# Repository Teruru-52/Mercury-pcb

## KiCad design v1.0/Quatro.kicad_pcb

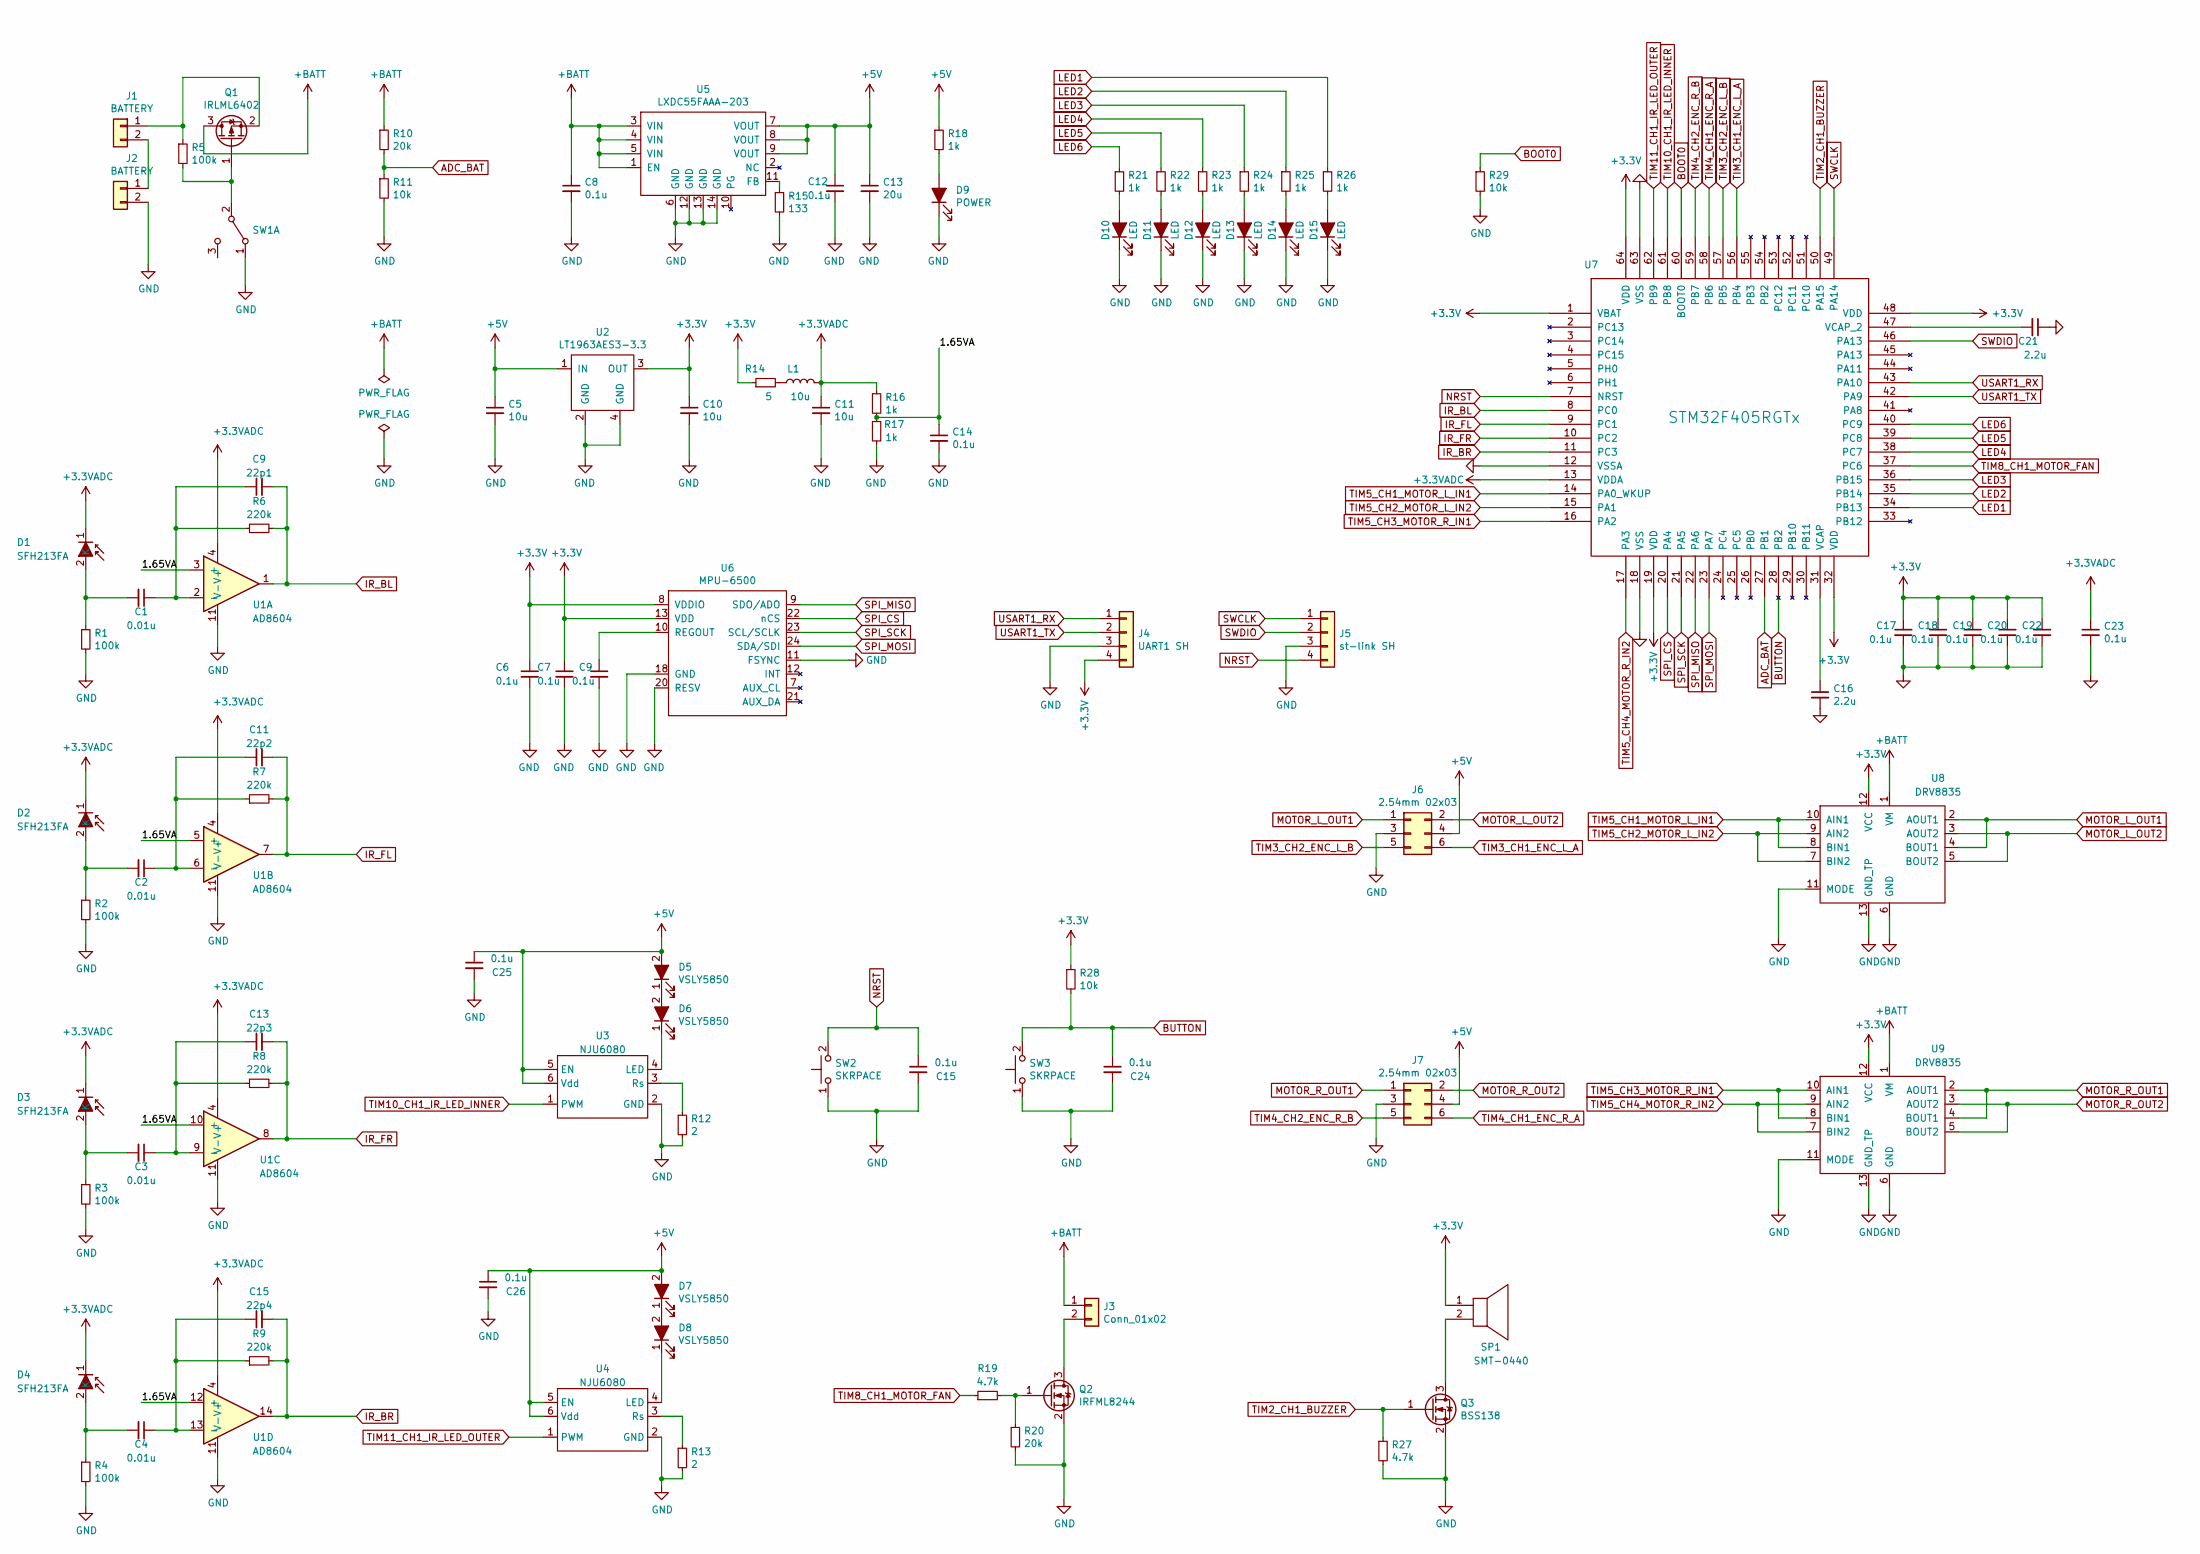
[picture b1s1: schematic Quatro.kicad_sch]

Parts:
22p1: C9; C_0603_1608Metric_Pad1.08x0.95mm_HandSolder
22p2: C11; C_0603_1608Metric_Pad1.08x0.95mm_HandSolder
22p3: C13; C_0603_1608Metric_Pad1.08x0.95mm_HandSolder
22p4: C15; C_0603_1608Metric_Pad1.08x0.95mm_HandSolder
C1, C2, C3, C4: 0.01u; C_0603_1608Metric_Pad1.08x0.95mm_HandSolder
C5, C10, C11: 10u; C_0603_1608Metric_Pad1.08x0.95mm_HandSolder
C6, C7, C8, C9, C12, C14, C15, C17, C18, C19, C20, C22, C23, C24, C25, C26: 0.1u; C_0603_1608Metric_Pad1.08x0.95mm_HandSolder
C13: 20u; C_0603_1608Metric_Pad1.08x0.95mm_HandSolder
C16, C21: 2.2u; C_0603_1608Metric_Pad1.08x0.95mm_HandSolder
D1, D2, D3, D4: SFH213FA; D_T-1_P2.54mm_Vertical_AnodeUp
D5, D6, D7, D8: VSLY5850; D_T-1_P2.54mm_Vertical_AnodeUp
D9: POWER; LED_0603_1608Metric_Pad1.05x0.95mm_HandSolder
D10, D11, D12, D13, D14, D15: LED; LED_0603_1608Metric_Pad1.05x0.95mm_HandSolder
J1, J2: BATTERY; PinSocket_1x02_P1.27mm_Vertical
J3: Conn_01x02; PinSocket_1x02_P1.27mm_Vertical
J4: UART1 SH; PinHeader_1x04_P2.54mm_Vertical
J5: st-link SH; JST_SH_BM04B-SRSS-TB_1x04-1MP_P1.00mm_Vertical
J6, J7: 2.54mm 02x03; PinHeader_2x03_P2.54mm_Vertical
L1: 10u; L_1210_3225Metric_Pad1.42x2.65mm_HandSolder
Q1: IRLML6402; SOT-23
Q2: IRFML8244; SOT-23
Q3: BSS138; SOT-23
R1, R2, R3, R4, R5: 100k; R_0805_2012Metric_Pad1.20x1.40mm_HandSolder
R6, R7, R8, R9: 220k; R_0603_1608Metric_Pad0.98x0.95mm_HandSolder
R10, R20: 20k; R_0603_1608Metric_Pad0.98x0.95mm_HandSolder
R11, R29: 10k; R_0805_2012Metric_Pad1.20x1.40mm_HandSolder
R12, R13: 2; R_0805_2012Metric_Pad1.20x1.40mm_HandSolder
R14: 5; R_0805_2012Metric_Pad1.20x1.40mm_HandSolder
R15: 133; R_1206_3216Metric_Pad1.30x1.75mm_HandSolder
R16, R17, R18, R21, R22, R23, R24, R25, R26: 1k; R_0805_2012Metric_Pad1.20x1.40mm_HandSolder
R19, R27: 4.7k; R_0603_1608Metric_Pad0.98x0.95mm_HandSolder
R28: 10k; R_0603_1608Metric_Pad0.98x0.95mm_HandSolder
SP1: SMT-0440; SMT-0440-T-R
SW1: SW_DPDT_x2; SlideSwitch
SW2, SW3: SKRPACE; SW_Push_1P1T_NO_Vertical_Wuerth_434133025816
U1: AD8604; TSSOP-14_4.4x5mm_P0.65mm
U2: LT1963AES3-3.3; SOT-223
U3, U4: NJU6080; SOT-23-6_Handsoldering
U5: LXDC55FAAA-203
U6: MPU-6500; QFN-24-1EP_3x3mm_P0.4mm_EP1.75x1.6mm
U7: STM32F405RGTx; LQFP-64_10x10mm_P0.5mm
U8, U9: DRV8835

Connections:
+3.3V: C6.1, C7.1, C10.1, C17.1, C18.1, C19.1, C20.1, C22.1, J4.4, R14.1, R28.1, SP1.1, U2.3 (OUT), U6.8 (VDDIO), U6.13 (VDD), U7.1 (VBAT), U7.19 (VDD), U7.32 (VDD), U7.48 (VDD), U7.64 (VDD), U8.12 (VCC), U9.12 (VCC)
+3.3VADC: C11.1, C23.1, D1.1 (K), D2.1 (K), D3.1 (K), D4.1 (K), L1.2, R16.1, U1.4 (V+), U7.13 (VDDA)
+5V: C5.1, C12.1, C13.1, C25.1, C26.1, D5.2, D7.2, J6.4, J7.4, R18.1, U2.1 (IN), U3.5 (EN), U3.6 (Vdd), U4.5 (EN), U4.6 (Vdd), U5.7 (VOUT), U5.8 (VOUT), U5.9 (VOUT)
+BATT: C8.1, J3.1, Q1.3 (D), R10.1, U5.1 (EN), U5.3 (VIN), U5.4 (VIN), U5.5 (VIN), U8.1 (VM), U9.1 (VM)
/1.65VA: C14.1, R16.2, R17.1, U1.3 (+), U1.5 (+), U1.10 (+), U1.12 (+)
ADC_BAT: R10.2, R11.1, U7.27 (PB1)
BOOT0: R29.1, U7.60 (BOOT0)
BUTTON: C24.1, R28.2, SW3.2, U7.28 (PB2)
GND: C5.2, C6.2, C7.2, C8.2, C9.2, C10.2, C11.2, C12.2, C13.2, C14.2, C15.2, C16.2, C17.2, C18.2, C19.2, C20.2, C21.1, C22.2, C23.2, C24.2, C25.2, C26.2, D9.1 (K), D10.1 (K), D11.1 (K), D12.1 (K), D13.1 (K), D14.1 (K), D15.1 (K), J2.2, J4.3, J5.3, J6.3, J7.3, Q2.2, Q3.2 (S), R1.2, R2.2, R3.2, R4.2, R11.2, R12.2, R13.2, R15.2, R17.2, R20.2, R27.2, R29.2, SW1.1 (A), SW2.1, SW3.1, U1.11 (V-), U2.2 (GND), U2.4 (GND), U3.2 (GND), U4.2 (GND), U5.6 (GND), U5.12 (GND), U5.13 (GND), U5.14 (GND), U6.11 (FSYNC), U6.18 (GND), U6.20 (RESV), U7.12 (VSSA), U7.18 (VSS), U7.63 (VSS), U8.6 (GND), U8.11 (MODE), U8.13 (GND_TP), U9.6 (GND), U9.11 (MODE), U9.13 (GND_TP)
IR_BL: 22p1.2, R6.2, U1.1, U7.8 (PC0)
IR_BR: 22p4.2, R9.2, U1.14, U7.11 (PC3)
IR_FL: 22p2.2, R7.2, U1.7, U7.9 (PC1)
IR_FR: 22p3.2, R8.2, U1.8, U7.10 (PC2)
LED1: R26.1, U7.34 (PB13)
LED2: R25.1, U7.35 (PB14)
LED3: R24.1, U7.36 (PB15)
LED4: R23.1, U7.38 (PC7)
LED5: R22.1, U7.39 (PC8)
LED6: R21.1, U7.40 (PC9)
MOTOR_L_OUT1: J6.1, U8.2 (AOUT1), U8.4 (BOUT1)
MOTOR_L_OUT2: J6.2, U8.3 (AOUT2), U8.5 (BOUT2)
MOTOR_R_OUT1: J7.1, U9.2 (AOUT1), U9.4 (BOUT1)
MOTOR_R_OUT2: J7.2, U9.3 (AOUT2), U9.5 (BOUT2)
NRST: C15.1, J5.4, SW2.2, U7.7 (NRST)
unnamed: 22p1.1, C1.1, R6.1, U1.2 (-)
unnamed: 22p2.1, C2.1, R7.1, U1.6 (-)
unnamed: 22p3.1, C3.1, R8.1, U1.9 (-)
unnamed: 22p4.1, C4.1, R9.1, U1.13 (-)
unnamed: C1.2, D1.2, R1.1
unnamed: C2.2, D2.2, R2.1
unnamed: C3.2, D3.2, R3.1
unnamed: C4.2, D4.2, R4.1
unnamed: C9.1, U6.10 (REGOUT)
unnamed: C16.1, U7.31 (VCAP)
unnamed: C21.2, U7.47 (VCAP_2)
unnamed: D5.1, D6.2
unnamed: D6.1, U3.4 (LED)
unnamed: D7.1, D8.2
unnamed: D8.1, U4.4 (LED)
unnamed: D9.2 (A), R18.2
unnamed: D10.2 (A), R21.2
unnamed: D11.2 (A), R22.2
unnamed: D12.2 (A), R23.2
unnamed: D13.2 (A), R24.2
unnamed: D14.2 (A), R25.2
unnamed: D15.2 (A), R26.2
unnamed: J1.1, Q1.2 (S), R5.1
unnamed: J1.2, J2.1
unnamed: J3.2, Q2.3
unnamed: L1.1, R14.2
unnamed: Q1.1 (G), R5.2, SW1.2 (B)
unnamed: Q2.1, R19.2, R20.1
unnamed: Q3.3 (D), SP1.2
unnamed: R12.1, U3.3 (Rs)
unnamed: R13.1, U4.3 (Rs)
unnamed: R15.1, U5.11 (FB)
SPI_CS: U6.22 (nCS), U7.20 (PA4)
SPI_MISO: U6.9 (SDO/ADO), U7.22 (PA6)
SPI_MOSI: U6.24 (SDA/SDI), U7.23 (PA7)
SPI_SCK: U6.23 (SCL/SCLK), U7.21 (PA5)
SWCLK: J5.1, U7.49 (PA14)
SWDIO: J5.2, U7.46 (PA13)
TIM2_CH1_BUZZER: Q3.1 (G), R27.1, U7.50 (PA15)
TIM3_CH1_ENC_L_A: J6.6, U7.56 (PB4)
TIM3_CH2_ENC_L_B: J6.5, U7.57 (PB5)
TIM4_CH1_ENC_R_A: J7.6, U7.58 (PB6)
TIM4_CH2_ENC_R_B: J7.5, U7.59 (PB7)
TIM5_CH1_MOTOR_L_IN1: U7.14 (PA0_WKUP), U8.8 (BIN1), U8.10 (AIN1)
TIM5_CH2_MOTOR_L_IN2: U7.15 (PA1), U8.7 (BIN2), U8.9 (AIN2)
TIM5_CH3_MOTOR_R_IN1: U7.16 (PA2), U9.8 (BIN1), U9.10 (AIN1)
TIM5_CH4_MOTOR_R_IN2: U7.17 (PA3), U9.7 (BIN2), U9.9 (AIN2)
TIM8_CH1_MOTOR_FAN: R19.1, U7.37 (PC6)
TIM10_CH1_IR_LED_INNER: U3.1 (PWM), U7.61 (PB8)
TIM11_CH1_IR_LED_OUTER: U4.1 (PWM), U7.62 (PB9)
USART1_RX: J4.1, U7.43 (PA10)
USART1_TX: J4.2, U7.42 (PA9)

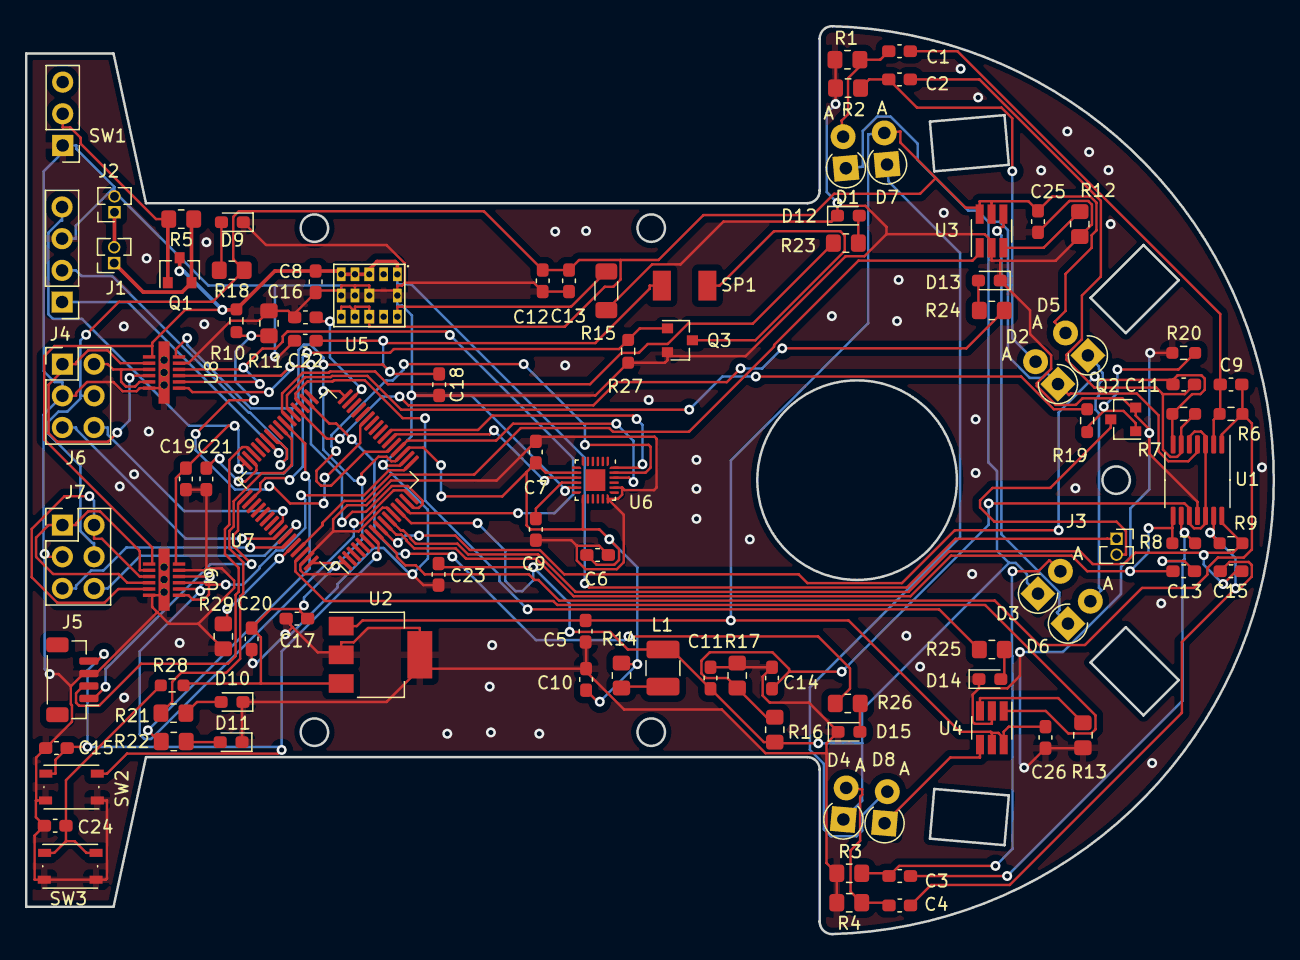
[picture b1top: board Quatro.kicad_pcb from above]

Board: 2 copper layers, 100.0 x 72.8 mm, 98 parts (0 on the bottom side), 76 nets.

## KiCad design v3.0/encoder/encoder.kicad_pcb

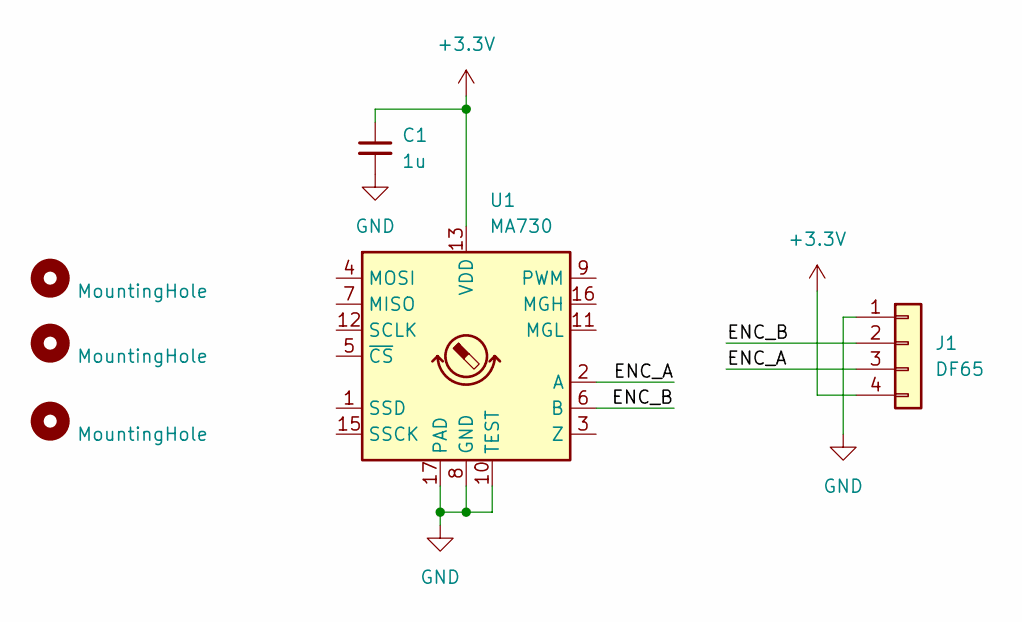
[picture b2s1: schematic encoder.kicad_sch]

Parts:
C1: 1u; C_0603_1608Metric
H1, H2, H3: MountingHole; MountingHole_2.2mm_M2
J1: DF65; DF65-4P
U1: MA730; QFN-16-1EP_3x3mm_P0.5mm_EP1.75x1.75mm

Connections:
+3.3V: C1.1, J1.4, U1.13 (VDD)
/ENC_A: J1.3, U1.2 (A)
/ENC_B: J1.2, U1.6 (B)
GND: C1.2, J1.1, U1.8 (GND), U1.10 (TEST), U1.17 (PAD)

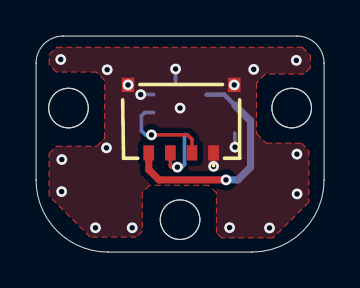
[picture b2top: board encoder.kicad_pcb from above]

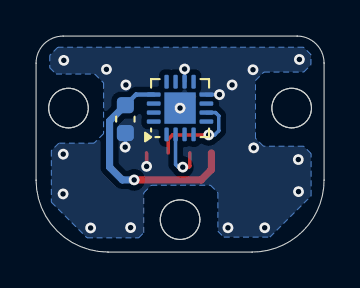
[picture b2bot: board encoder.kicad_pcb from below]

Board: 2 copper layers, 16.0 x 12.0 mm, 6 parts (2 on the bottom side), 4 nets.

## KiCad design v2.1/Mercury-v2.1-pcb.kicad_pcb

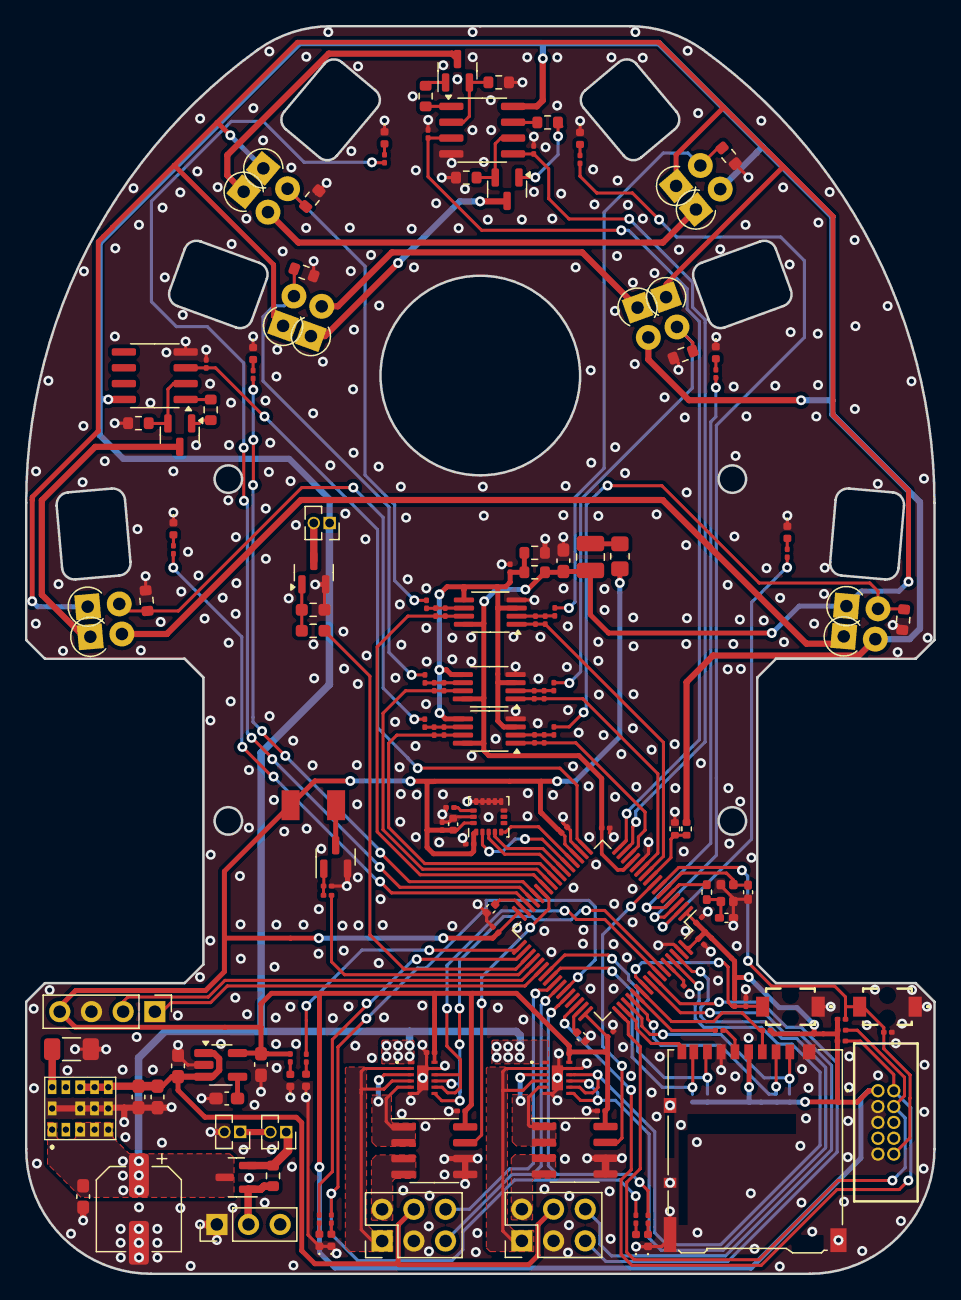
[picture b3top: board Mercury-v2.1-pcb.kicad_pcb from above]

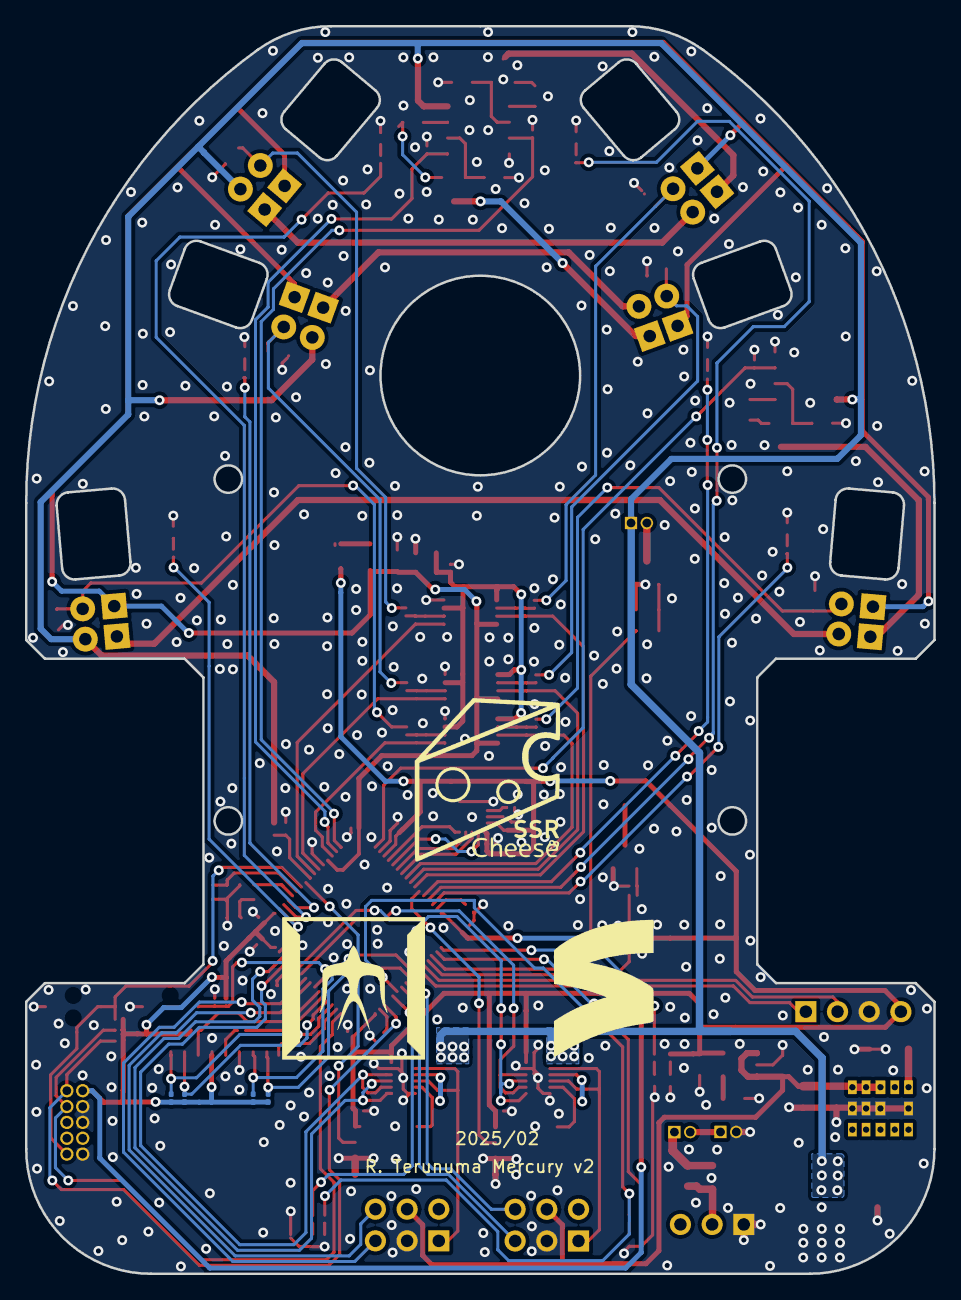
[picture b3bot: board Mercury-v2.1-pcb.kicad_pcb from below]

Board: 2 copper layers, 72.8 x 100.0 mm, 154 parts (4 on the bottom side), 118 nets.

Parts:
C1, C6, C22: 2.2u; C_0402_1005Metric
C2, C3, C5, C7, C8, C10, C11, C12, C17, C18, C19, C21, C30, C39, C40: 0.1u; C_0201_0603Metric
C4, C9: 10p; C_0402_1005Metric_Pad0.74x0.62mm_HandSolder
C13, C15, C20, C31, C33, C35, C37: 0.01u; C_0201_0603Metric
C14, C16, C32, C34, C36, C38: 22p; C_0201_0603Metric
C23: 100uF; CP_Elec_6.3x3
C25, C27: 0.1u; C_0603_1608Metric_Pad1.08x0.95mm_HandSolder
C28: 20u; C_0603_1608Metric_Pad1.08x0.95mm_HandSolder
C29: 10u; C_0603_1608Metric_Pad1.08x0.95mm_HandSolder
C41, C43: 1u; C_0603_1608Metric_Pad1.08x0.95mm_HandSolder
C42: 0.01u; C_0603_1608Metric_Pad1.08x0.95mm_HandSolder
D1, D2, D3, D4, D5, D6, D7, D8, D9, D10, D11: LED; LED_0402_1005Metric
D12, D13, D19, D20, D21, D22: SFH213FA; D_T-1_P2.54mm_Vertical_AnodeUp
D14, D15, D16, D17, D23, D24: VSLY5850; D_T-1_P2.54mm_Vertical_AnodeUp
D18: POWER; LED_0402_1005Metric
J1: Micro_SD_Card_Det2; microSD_HC_Hirose_DM3AT-SF-PEJM5
J2: UART; PinHeader_1x04_P2.54mm_Vertical
J3: Conn_ARM_JTAG_SWD_10; mylib
J4, J7: 2.54mm 02x03; PinHeader_2x03_P2.54mm_Vertical
J5, J6: BATTERY; PinSocket_1x02_P1.27mm_Vertical
J8: Conn_01x02; PinSocket_1x02_P1.27mm_Vertical
L1: 10u; L_1008_2520Metric
Q1: BSS138; SOT-23
Q2, Q3, Q5, Q6: IRFML8244; SOT-23
Q4: IRLML6402; SOT-23
R1, R4, R5, R12, R15, R18, R24, R27, R46, R51, R52, R53, R54, R55: 10k; R_0201_0603Metric
R2: 1k; R_0402_1005Metric_Pad0.72x0.64mm_HandSolder
R3: 120; R_0201_0603Metric
R6, R7, R8, R9, R10, R11, R13, R14, R16, R17, R19, R33: 1k; R_0201_0603Metric
R20, R22, R30, R38, R40, R42, R44: 100k; R_0603_1608Metric
R21, R23, R39, R41, R43, R45: 220k; R_0201_0603Metric
R25, R28, R47: 10; R_0603_1608Metric
R26, R29, R48: 33 1% 1/2W; R_0603_1608Metric
R31: 20k; R_0402_1005Metric
R32: 10k; R_0402_1005Metric
R34: 133; R_1206_3216Metric_Pad1.30x1.75mm_HandSolder
R35: 5; R_0805_2012Metric_Pad1.20x1.40mm_HandSolder
R36, R37: 1k; R_0603_1608Metric
R49: 4.7k; R_0603_1608Metric_Pad0.98x0.95mm_HandSolder
R50: 20k; R_0603_1608Metric_Pad0.98x0.95mm_HandSolder
R56: 33; R_0201_0603Metric
SP1: SMT-0440
SW1, SW2: Switch; TVAF06A020BR
SW3: SW_DPDT_x2; PinHeader_1x03_P2.54mm_Vertical
U1: STM32F405RGTx; LQFP-64_10x10mm_P0.5mm
U2, U9, U10: AD8602; MSOP-8_3x3mm_P0.65mm
U3, U11: DRV8835; DRV8835DSSR
U4, U12: ACS722xLCTR-05AB; SOIC-8_3.9x4.9mm_P1.27mm
U5: ICM-20602; LGA-16_3x3mm_P0.5mm_LayoutBorder3x5y
U6, U13: SOIC-8_3.9x4.9mm_P1.27mm
U8: LXDC55FAAA-203; LXDC55FAAA203
U14: NJM12877F33-TE1; SOT-23-5_HandSoldering
Y1: XRCGB16M000FXN02R0

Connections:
+1.65VADC: C30.1, R36.2, R37.1, U2.3 (+), U2.5 (+), U9.3 (+), U9.5 (+), U10.3 (+), U10.5 (+)
+3.3V: C2.1, C3.1, C5.1, C7.1, C8.1, C17.1, C18.1, C20.1, C21.1, C22.1, C39.1, C40.1, C43.1, J1.4 (VDD), J2.4, J3.1 (VTref), R5.1, R12.1, R15.1, R18.1, R33.1, R35.1, R51.1, R52.1, R53.1, R54.1, R55.1, SP1.1, U1.1 (VBAT), U1.19 (VDD), U1.32 (VDD), U1.48 (VDD), U1.64 (VDD), U3.12 (VCC), U4.8 (VCC), U5.1 (VDDIO), U5.16 (VDD), U11.12 (VCC), U12.8 (VCC), U14.5 (VOUT)
+3.3VADC: C10.1, C29.1, D12.1 (K), D13.1 (K), D19.1 (K), D20.1 (K), D21.1 (K), D22.1 (K), L1.2, R36.1, U1.13 (VDDA), U2.8 (V+), U9.8 (V+), U10.8 (V+)
+5V: C27.1, C28.1, C41.1, J4.4, J7.4, U8.7 (VOUT), U8.8 (VOUT), U8.9 (VOUT), U14.1 (VIN), U14.3 (CONTROL)
+BATT: C23.1, C25.1, D14.2 (A), D16.2 (A), D23.2 (A), J8.1, Q4.3 (D), R31.1, U3.1 (VM), U6.8 (V+), U8.1 (EN), U8.3 (VIN), U8.4 (VIN), U8.5 (VIN), U11.1 (VM), U13.8 (V+)
/fan_driver/MOTOR_FAN_EN: R49.1, U1.35 (PB14)
/imu/CS: U1.20 (PA4), U5.5 (~CS)
/imu/SDI: U1.23 (PA7), U5.3 (SDA/SDI)
/imu/SDO: U1.22 (PA6), U5.4 (SAO/SD0)
/imu/SPC: U1.21 (PA5), U5.2 (SCL/SPC)
/ir_led/IR_LED_IN1: R24.2, U1.16 (PA2), U6.3 (+)
/ir_led/IR_LED_IN2: R27.2, U1.15 (PA1), U6.5 (+)
/ir_led_single/IR_LED_IN: R46.2, U1.17 (PA3), U13.3 (+)
/ir_sensor1/IR_OUT_A: C32.2, R39.2, U1.11 (PC3), U9.1
/ir_sensor1/IR_OUT_B: C34.2, R41.2, U1.25 (PC5), U9.7
/ir_sensor2/IR_OUT_A: C36.2, R43.2, U1.10 (PC2), U10.1
/ir_sensor2/IR_OUT_B: C38.2, R45.2, U1.26 (PB0), U10.7
/ir_sensor/IR_OUT_A: C14.2, R21.2, U1.14 (PA0_WKUP), U2.1
/ir_sensor/IR_OUT_B: C16.2, R23.2, U1.24 (PC4), U2.7
/mcu/ACS_IN_L: U1.27 (PB1), U4.7 (VIOUT)
/mcu/ACS_IN_R: U1.8 (PC0), U12.7 (VIOUT)
/mcu/ADC_BAT: R31.2, R32.1, U1.9 (PC1)
/mcu/BOOT0: R1.1, U1.60 (BOOT0)
/mcu/BUZZER: R3.1, U1.36 (PB15)
/mcu/ENC_L_A: J4.6, U1.41 (PA8)
/mcu/ENC_R_A: J7.6, U1.56 (PB4)
/mcu/END_L_B: J4.5, U1.42 (PA9)
/mcu/END_R_B: J7.5, U1.57 (PB5)
/mcu/LED1: R6.1, U1.2 (PC13)
/mcu/LED2: R8.1, U1.3 (PC14)
/mcu/LED3: R10.1, U1.4 (PC15)
/mcu/LED4: R13.1, U1.28 (PB2)
/mcu/LED5: R16.1, U1.29 (PB10)
/mcu/LED6: R19.1, U1.30 (PB11)
/mcu/LED7: R7.1, U1.33 (PB12)
/mcu/LED8: R9.1, U1.34 (PB13)
/mcu/LED9: R11.1, R14.1, U1.43 (PA10)
/mcu/LED10: R17.1, U1.44 (PA11)
/mcu/MOTOR_L_IN1: U1.58 (PB6), U3.8 (BIN1), U3.10 (AIN1)
/mcu/MOTOR_L_IN2: U1.59 (PB7), U3.7 (BIN2), U3.9 (AIN2)
/mcu/MOTOR_R_IN1: U1.61 (PB8), U11.8 (BIN1), U11.10 (AIN1)
/mcu/MOTOR_R_IN2: U1.62 (PB9), U11.7 (BIN2), U11.9 (AIN2)
/mcu/NRST: C11.1, J3.10 (~RESET), R12.2, SW1.2, U1.7 (NRST)
/mcu/OSC_IN: R2.1, U1.5 (PH0)
/mcu/OSC_OUT: C9.1, U1.6 (PH1), Y1.3
/mcu/SDIO_CK: R56.1, U1.53 (PC12)
/mcu/SDIO_CMD: J1.3 (CMD), R53.2, U1.54 (PB2)
/mcu/SDIO_D0: J1.7 (DAT0), R52.2, U1.39 (PC8)
/mcu/SDIO_D1: J1.8 (DAT1), R51.2, U1.40 (PC9)
/mcu/SDIO_D2: J1.1 (DAT2), R55.2, U1.51 (PC10)
/mcu/SDIO_D3: J1.2 (DAT3/CD), R54.2, U1.52 (PC11)
/mcu/SDIO_SW: J1.9 (DET_B), U1.50 (PA15)
/mcu/SW: C12.1, R5.2, SW2.2, U1.55 (PB3)
/mcu/SWCLK: J3.4 (SWDCLK/TCK), R15.2, U1.49 (PA14)
/mcu/SWDIO: J3.2 (SWDIO/TMS), R18.2, U1.46 (PA13)
/mcu/USART6_RX: J2.1, U1.38 (PC7)
/mcu/USART6_TX: J2.2, U1.37 (PC6)
/motor_driver L/ACS_IN2: U3.3 (AOUT2), U3.5 (BOUT2), U4.1 (IP+), U4.2 (IP+)
/motor_driver L/MOTOR_OUT1: J4.1, U3.2 (AOUT1), U3.4 (BOUT1)
/motor_driver L/MOTOR_OUT2: J4.2, U4.3 (IP-), U4.4 (IP-)
/motor_driver R/ACS_IN2: U11.3 (AOUT2), U11.5 (BOUT2), U12.1 (IP+), U12.2 (IP+)
/motor_driver R/MOTOR_OUT1: J7.1, U11.2 (AOUT1), U11.4 (BOUT1)
/motor_driver R/MOTOR_OUT2: J7.2, U12.3 (IP-), U12.4 (IP-)
GND: C1.2, C2.2, C3.2, C4.2, C5.2, C6.1, C7.2, C8.2, C9.2, C10.2, C11.2, C12.2, C17.2, C18.2, C19.2, C20.2, C21.2, C22.2, C23.2, C25.2, C27.2, C28.2, C29.2, C30.2, C39.2, C40.2, C41.2, C42.2, C43.2, D1.1 (K), D2.1 (K), D3.1 (K), D4.1 (K), D5.1 (K), D6.1 (K), D7.1 (K), D8.1 (K), D9.1 (K), D10.1 (K), D11.1 (K), D18.1 (K), J1.6 (VSS), J1.10 (DET_A), J1.11 (SHIELD), J2.3, J3.3 (GND), J3.5 (GND), J3.9 (GNDDetect), J4.3, J6.2, J7.3, Q1.2 (S), Q6.2, R1.2, R4.2, R20.2, R22.2, R24.1, R26.2, R27.1, R29.2, R32.2, R34.2, R37.2, R38.2, R40.2, R42.2, R44.2, R46.1, R48.2, R50.2, SW1.1, SW2.1, SW3.1 (A), U1.12 (VSSA), U1.18 (VSS), U1.63 (VSS), U2.4 (V-), U3.6 (GND), U3.11 (MODE), U3.13 (GND_TP), U4.5 (GND), U4.6 (BW_SEL), U5.8 (FSYNC), U5.9 (GND), U5.10 (GND), U5.11 (GND), U5.12 (GND), U5.13 (GND), U5.15 (GND), U6.4 (V-), U8.6 (GND), U8.12 (GND), U8.13 (GND), U8.14 (GND), U9.4 (V-), U10.4 (V-), U11.6 (GND), U11.11 (MODE), U11.13 (GND_TP), U12.5 (GND), U12.6 (BW_SEL), U13.4 (V-), U14.2 (GND), Y1.2
unnamed: C4.1, R2.2, Y1.1
unnamed: C13.2, D13.2, R22.1
unnamed: C15.2, D12.2, R20.1
unnamed: C31.2, D20.2, R40.1
unnamed: C33.2, D19.2, R38.1
unnamed: C35.2, D22.2, R44.1
unnamed: C37.2, D21.2, R42.1
unnamed: D1.2 (A), R6.2
unnamed: D2.2 (A), R7.2
unnamed: D3.2 (A), R8.2
unnamed: D4.2 (A), R9.2
unnamed: D5.2 (A), R10.2
unnamed: D6.2 (A), R11.2
unnamed: D7.2 (A), R13.2
unnamed: D8.2 (A), R14.2
unnamed: D9.2 (A), R16.2
unnamed: D10.2 (A), R17.2
unnamed: D11.2 (A), R19.2
unnamed: D14.1 (K), D15.2 (A)
unnamed: D15.1 (K), Q2.3 (D)
unnamed: D16.1 (K), D17.2 (A)
unnamed: D17.1 (K), Q3.3 (D)
unnamed: D18.2 (A), R33.2
unnamed: D23.1 (K), D24.2 (A)
unnamed: D24.1 (K), Q5.3 (D)
unnamed: J1.5 (CLK), R56.2
unnamed: J5.1, Q4.2 (S), R30.1
unnamed: J5.2, J6.1
unnamed: J8.2, Q6.3
unnamed: L1.1, R35.2
unnamed: Q1.3 (D), SP1.2
unnamed: Q1.1 (G), R3.2, R4.1
unnamed: Q2.1 (G), R25.1
unnamed: Q2.2 (S), R26.1, U6.2 (-)
unnamed: Q3.1 (G), R28.1
unnamed: Q3.2 (S), R29.1, U6.6 (-)
unnamed: Q4.1 (G), R30.2, SW3.2 (B)
unnamed: Q5.1 (G), R47.1
unnamed: Q5.2 (S), R48.1, U13.2 (-)
unnamed: Q6.1, R49.2, R50.1
unnamed: R25.2, U6.1
unnamed: R28.2, U6.7
unnamed: R47.2, U13.1
unnamed: C1.1, U1.31 (VCAP)
unnamed: C6.2, U1.47 (VCAP_2)
unnamed: C13.1, C14.1, R21.1, U2.2 (-)
unnamed: C15.1, C16.1, R23.1, U2.6 (-)
unnamed: C19.1, U5.14 (REGOUT)
unnamed: R34.1, U8.11 (FB)
unnamed: C31.1, C32.1, R39.1, U9.2 (-)
unnamed: C33.1, C34.1, R41.1, U9.6 (-)
unnamed: C35.1, C36.1, R43.1, U10.2 (-)
unnamed: C37.1, C38.1, R45.1, U10.6 (-)
unnamed: C42.1, U14.4 (Cs)

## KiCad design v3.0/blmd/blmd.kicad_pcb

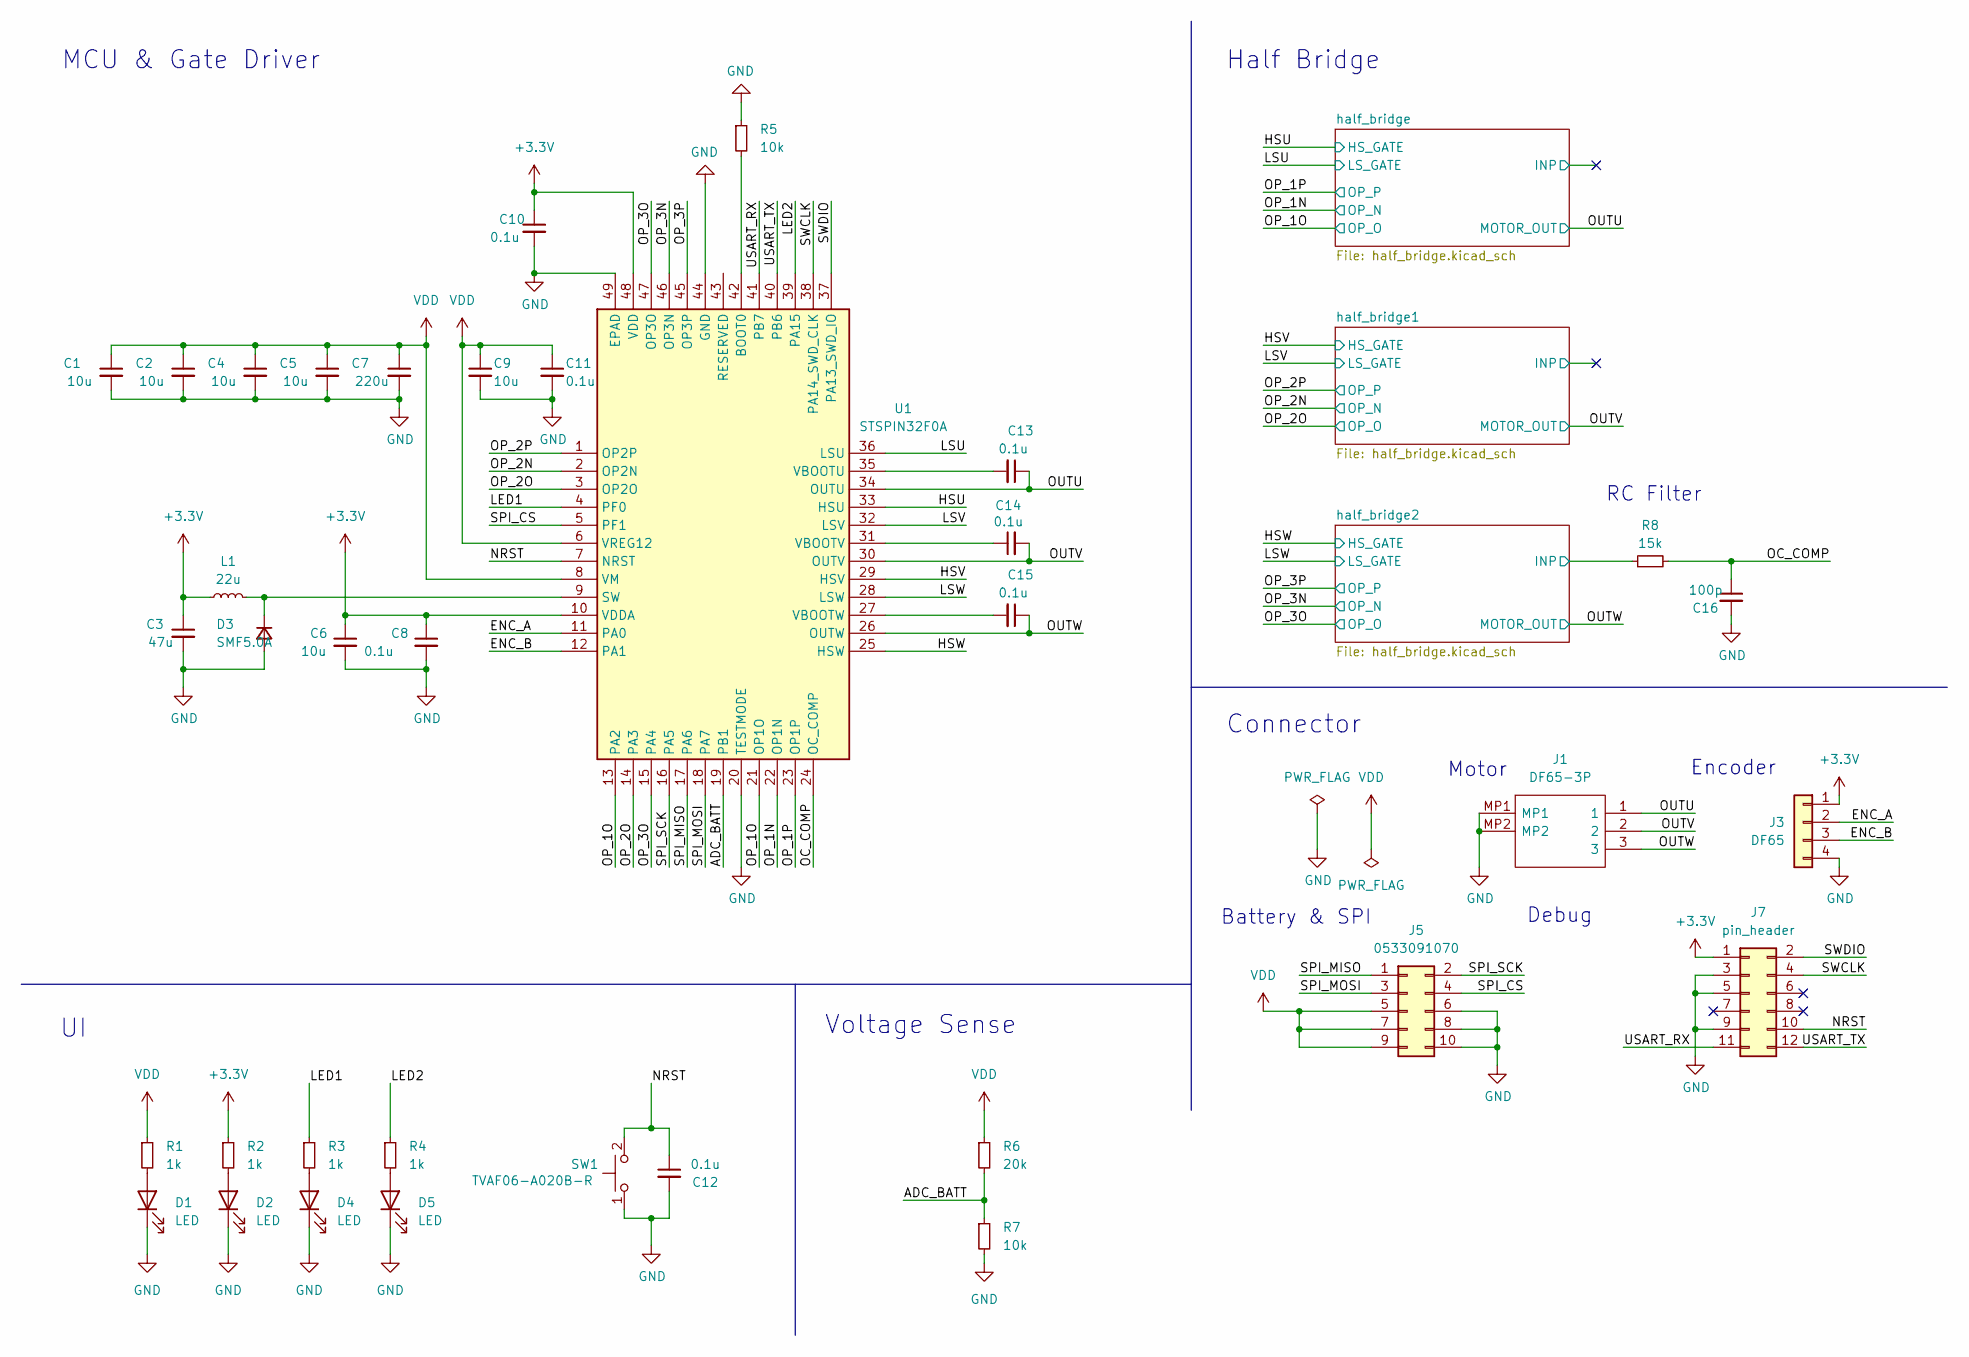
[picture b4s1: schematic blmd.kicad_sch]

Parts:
C1, C2, C4, C5: 10u; C_0805_2012Metric
C3: 47u; C_0603_1608Metric
C6: 10u; C_0402_1005Metric
C7: 220u; C_0805_2012Metric
C8, C10, C12, C13, C14, C15: 0.1u; C_0201_0603Metric
C9: 10u; C_0603_1608Metric
C11: 0.1u; C_0402_1005Metric
C16: 100p; C_0201_0603Metric
D1, D2, D4, D5: LED; LED_0402_1005Metric
D3: SMF5.0A; D_SOD-123F
J1: DF65-3P; DF653P17V78; Manufacturer_Part_Number DF65-3P-1.7V(78); Mouser Part Number 798-DF65-3P-1.7V(78)
J3: DF65; DF65-4P
J5: 0533091070
J7: pin_header; PinHeader_2x06_P1.27mm_Vertical
L1: 22u; SRN3015
R1, R2, R3, R4: 1k; R_0201_0603Metric
R5, R7: 10k; R_0201_0603Metric
R6: 20k; R_0201_0603Metric
R8: 15k; R_0201_0603Metric
SW1: TVAF06-A020B-R; TVAF06A020BR
U1: STSPIN32F0A; QFN50P700X700X105-49N-D; Manufacturer_Part_Number STSPIN32F0A; Mouser Part Number 511-STSPIN32F0A

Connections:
+3.3V: C3.1, C6.1, C8.1, C10.1, J3.1, J7.1, L1.1, R2.1, U1.10 (VDDA), U1.48 (VDD); also elsewhere on the board
/ADC_BATT: R6.2, R7.1, U1.19 (PB1)
/ENC_A: J3.2, U1.11 (PA0)
/ENC_B: J3.3, U1.12 (PA1)
/HSU: U1.33 (HSU); also elsewhere on the board
/HSV: U1.29 (HSV); also elsewhere on the board
/HSW: U1.25 (HSW); also elsewhere on the board
/LED1: R3.1, U1.4 (PF0)
/LED2: R4.1, U1.39 (PA15)
/LSU: U1.36 (LSU); also elsewhere on the board
/LSV: U1.32 (LSV); also elsewhere on the board
/LSW: U1.28 (LSW); also elsewhere on the board
/NRST: C12.1, J7.10, SW1.2, U1.7 (NRST)
/OC_COMP: C16.1, R8.2, U1.24 (OC_COMP)
/OP_1N: U1.22 (OP1N); also elsewhere on the board
/OP_1O: U1.13 (PA2), U1.21 (OP1O); also elsewhere on the board
/OP_1P: U1.23 (OP1P); also elsewhere on the board
/OP_2N: U1.2 (OP2N); also elsewhere on the board
/OP_2O: U1.3 (OP2O), U1.14 (PA3); also elsewhere on the board
/OP_2P: U1.1 (OP2P); also elsewhere on the board
/OP_3N: U1.46 (OP3N); also elsewhere on the board
/OP_3O: U1.15 (PA4), U1.47 (OP3O); also elsewhere on the board
/OP_3P: U1.45 (OP3P); also elsewhere on the board
/OUTU: C13.1, J1.1, U1.34 (OUTU); also elsewhere on the board
/OUTV: C14.2, J1.2, U1.30 (OUTV); also elsewhere on the board
/OUTW: C15.1, J1.3, U1.26 (OUTW); also elsewhere on the board
/SPI_CS: J5.4, U1.5 (PF1)
/SPI_MISO: J5.1, U1.17 (PA6)
/SPI_MOSI: J5.3, U1.18 (PA7)
/SPI_SCK: J5.2, U1.16 (PA5)
/SWCLK: J7.4, U1.38 (PA14_SWD_CLK)
/SWDIO: J7.2, U1.37 (PA13_SWD_IO)
/USART_RX: J7.11, U1.41 (PB7)
/USART_TX: J7.12, U1.40 (PB6)
/half_bridge2/INP: R8.1; also elsewhere on the board
GND: C1.2, C2.2, C3.2, C4.2, C5.2, C6.2, C7.2, C8.2, C9.2, C10.2, C11.2, C12.2, C16.2, D1.1 (K), D2.1 (K), D3.2 (A), D4.1 (K), D5.1 (K), J1.MP1, J1.MP2, J3.4, J5.6, J5.8, J5.10, J7.3, J7.5, J7.9, R5.1, R7.2, SW1.1, U1.20 (TESTMODE), U1.44 (GND), U1.49 (EPAD); also elsewhere on the board
unnamed: D1.2 (A), R1.2
unnamed: D2.2 (A), R2.2
unnamed: D3.1 (K), L1.2, U1.9 (SW)
unnamed: D4.2 (A), R3.2
unnamed: D5.2 (A), R4.2
unnamed: R5.2, U1.42 (BOOT0)
unnamed: C13.2, U1.35 (VBOOTU)
unnamed: C14.1, U1.31 (VBOOTV)
unnamed: C15.2, U1.27 (VBOOTW)
VDD: C1.1, C2.1, C4.1, C5.1, C7.1, C9.1, C11.1, J5.5, J5.7, J5.9, R1.1, R6.1, U1.6 (VREG12), U1.8 (VM); also elsewhere on the board

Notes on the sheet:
RC Filter
MCU & Gate Driver
Connector
Voltage Sense
Battery & SPI
Half Bridge
Debug
Encoder
Motor
